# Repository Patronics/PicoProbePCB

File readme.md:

# PicoProbePCB
A simple, minimal PCB for making a [Rasberry Pi debug probe](https://github.com/raspberrypi/debugprobe) (formerly called PicoProbe), designed for ease of machining with a single layer, yet with optional additional features (A power LED and some power breakouts) if produced as a two-layer PCB.  

### Design
|Schematic   |   PCB Layout   |   Single Layer Layout   |
|:-------:   |    :------:    |   :-----------------:   |
||||

### Images
| Rev 2  PCB Render   |  Rev 1 single-sided (off) | Rev 1 single-sided (active)|
| :---: | :---: | :---:|
|| ||

The single-sided version was machined using my homemade CNC Machine

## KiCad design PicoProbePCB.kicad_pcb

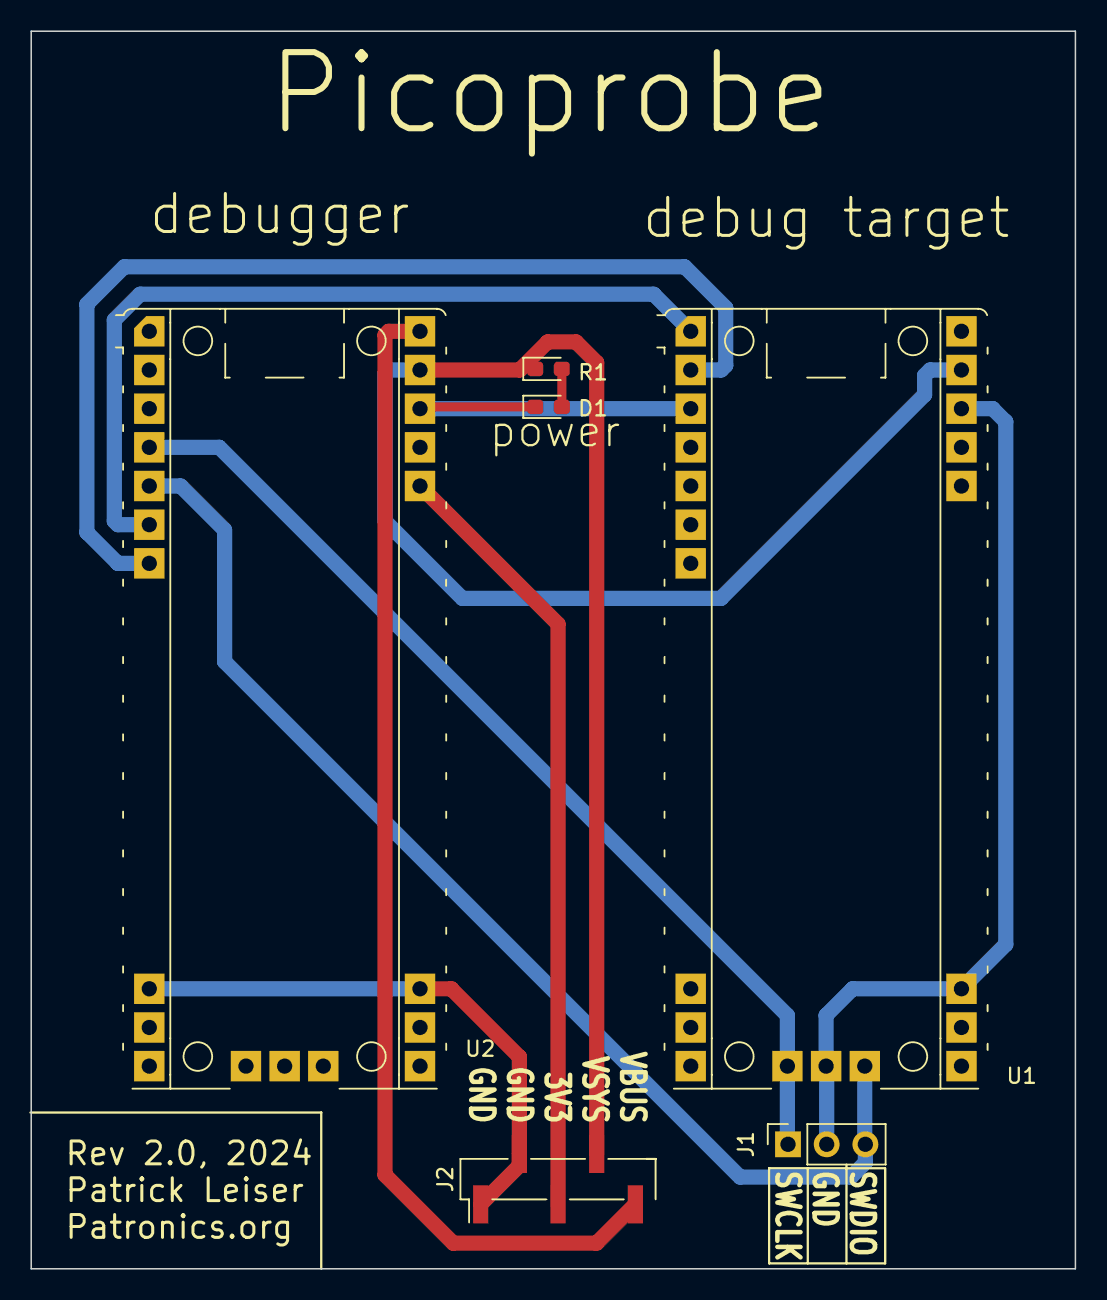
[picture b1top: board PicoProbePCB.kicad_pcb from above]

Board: 2 copper layers, 68.6 x 81.3 mm, 6 parts (0 on the bottom side), 9 nets.

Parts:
D1: LED; LED_0603_1608Metric_Pad1.05x0.95mm_HandSolder
J1: Conn_01x03_Socket; PinSocket_1x03_P2.54mm_Vertical
J2: Conn_01x05; PinHeader_1x05_P2.54mm_Vertical_SMD_Pin1Left
R1: R; LED_0603_1608Metric_Pad1.05x0.95mm_HandSolder
U1: RaspberryPi_Pico_SecondaryPins; RaspberryPi_Pico_Debug_PicoProbePinsOnlyLargePads
U2: RaspberryPi_Pico; RaspberryPi_Pico_Debug_PicoProbePinsOnlyLargePads

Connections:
+3V3: J2.3, U2.36 (3V3)
GND: D1.1 (K), J1.2, J2.1, J2.2, U1.3 (GND), U1.18 (GND), U1.23 (GND), U1.38 (GND), U1.D2 (GND), U2.3 (GND), U2.18 (GND), U2.23 (GND), U2.38 (GND)
unnamed: D1.2 (A), R1.2
unnamed: J1.1, U1.D1 (SWCLK), U2.4 (GPIO2)
unnamed: J1.3, U1.D3 (SWDIO), U2.5 (GPIO3)
unnamed: U1.1 (GPIO0), U2.6 (GPIO4)
unnamed: U1.2 (GPIO1), U2.7 (GPIO5)
VBUS: J2.5, U2.40 (VBUS)
VCC: J2.4, R1.1, U1.39 (VSYS), U2.39 (VSYS)

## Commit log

2024-02-24 Initial commit, second revision of layout, more angular and larger zones for easy machining
2024-02-24 add optional smt power led on top layer
2024-02-29 update to kicad 8.0 and add top-layer (optional) power rail breakout
2024-02-29 add readme and images
2024-02-29 fix spaces in image paths
2024-02-29 add photos and improve silkscreen for v2 board
2024-02-29 add gerbers and some minor fixes
2024-02-29 add single layer version of image
2024-02-29 fix readme formatting
2024-02-29 another readme formatting fix
2024-02-29 yet another readme formatting fix
2024-02-29 improve image crop
2024-02-29 resize images
2024-02-29 adjust readme
2026-05-31 Update readme.md with link to debugprobe
